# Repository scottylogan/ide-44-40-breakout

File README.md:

40 pin IDE breakout for 44 pin CF to IDE adapter

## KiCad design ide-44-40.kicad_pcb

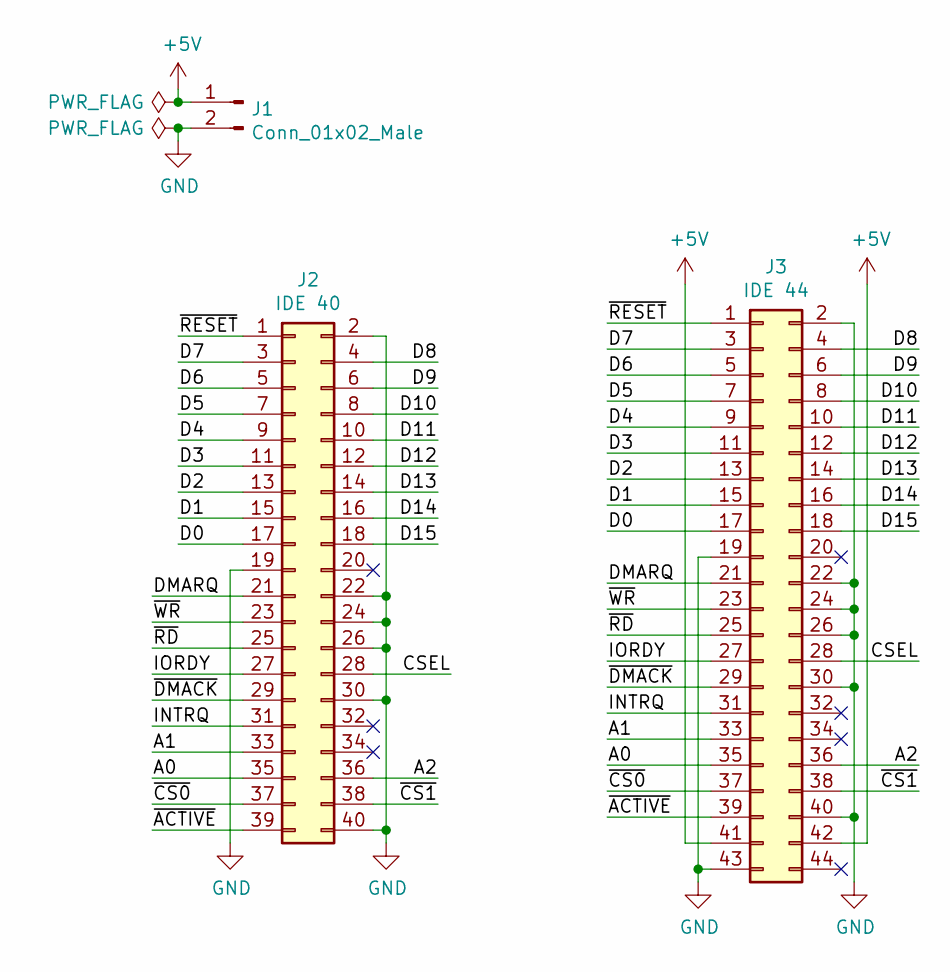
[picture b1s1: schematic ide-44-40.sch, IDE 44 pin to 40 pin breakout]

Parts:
J1: Conn_01x02_Male; PinHeader_1x02_P2.54mm_Vertical
J2: IDE 40; PinHeader_2x20_P2.54mm_Vertical
J3: IDE 44; PinSocket_2x22_P2.00mm_Horizontal

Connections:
+5V: J1.1, J3.41, J3.42
/A0: J2.35, J3.35
/A1: J2.33, J3.33
/A2: J2.36, J3.36
/CSEL: J2.28, J3.28
/D0: J2.17, J3.17
/D1: J2.15, J3.15
/D2: J2.13, J3.13
/D3: J2.11, J3.11
/D4: J2.9, J3.9
/D5: J2.7, J3.7
/D6: J2.5, J3.5
/D7: J2.3, J3.3
/D8: J2.4, J3.4
/D9: J2.6, J3.6
/D10: J2.8, J3.8
/D11: J2.10, J3.10
/D12: J2.12, J3.12
/D13: J2.14, J3.14
/D14: J2.16, J3.16
/D15: J2.18, J3.18
/DMARQ: J2.21, J3.21
/INTRQ: J2.31, J3.31
/IORDY: J2.27, J3.27
/~ACTIVE: J2.39, J3.39
/~CS0: J2.37, J3.37
/~CS1: J2.38, J3.38
/~DMACK: J2.29, J3.29
/~RD: J2.25, J3.25
/~RESET: J2.1, J3.1
/~WR: J2.23, J3.23
GND: J1.2, J2.2, J2.19, J2.22, J2.24, J2.26, J2.30, J2.40, J3.2, J3.19, J3.22, J3.24, J3.26, J3.30, J3.40, J3.43

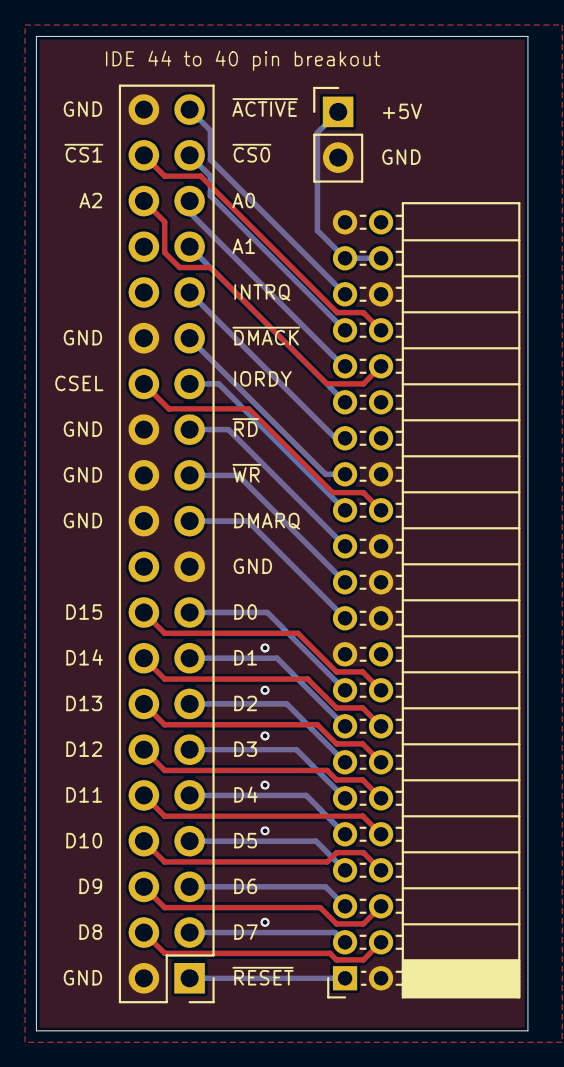
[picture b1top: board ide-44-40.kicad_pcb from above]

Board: 2 copper layers, 27.3 x 55.2 mm, 3 parts (0 on the bottom side), 32 nets.

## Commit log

2025-04-16 added LICENSE

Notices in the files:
ide-44-40.kicad_pcb:
© 2020, Scotty Logan
